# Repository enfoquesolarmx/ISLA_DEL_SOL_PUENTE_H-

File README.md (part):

# Isla del Sol — Puente H SPWM 48 V → 127 V / 60 Hz

Inversor / cargador de **puente H con modulación SPWM** para sistemas solares aislados: **48 V de batería → 127 V / 60 Hz, 1000 W**, con modo cargador de **1 kVA**.

El proyecto se publica como **referencia de estudio**: cada decisión de diseño está justificada y documentada (cálculos, hojas de datos, errores encontrados y cómo se corrigieron).

> ⚠️ **Advertencia de seguridad:** este equipo maneja corrientes altas en el lado de 48 V y **127 V AC en la salida, que pueden ser mortales**. Es un prototipo en desarrollo, no un producto certificado. Úsalo bajo tu propio riesgo y solo si tienes experiencia con electrónica de potencia.

---

*Tarjeta de potencia del puente H, prototipo de trinchera V0.1 (render 3D de KiCad). Detalles en [`hardware/puente_h/`](hardware/puente_h/README.md).*

*Tarjeta de transferencia de carga V0.1 (render 3D de KiCad): red / inversor / cargador con 5 relés y unión N–PE automática. Detalles en [`hardware/transferencia_reles/`](hardware/transferencia_reles/README.md).*

## Características principales

| Parámetro | Valor |
| --- | --- |
| Entrada | Batería de 48 V |
| Salida | 127 V / 60 Hz, 1000 W (transformador compatible 24–28 V / 120 V) |
| Modo inversor | Modulación híbrida: rama A a 24 kHz, rama B a 60 Hz |
| Modo cargador | Unipolar, ambas ramas a 24 kHz, 1 kVA |
| MOSFET | Infineon IRF100P219 (100 V), disipador Fischer SK 129 |
| Capacitores de bus | 4 × Rubycon 100ZLH820MEFC18X40 |
| Filtro de salida | ~2 mH (dispersión + inductor de ferrita E65 N87) + 4.7 µF MKP X2 |

---

## Gate drivers universales

Los módulos de gate driver son **intercambiables**: usan los mismos conectores (J1 hacia la tarjeta de control, J5 hacia el puente H) y **el mismo firmware**.

| Módulo | Tecnología | Tiempo muerto | Para qué | Estado |
| --- | --- | --- | --- | --- |
| IRS2186 | Driver de bootstrap | 500 ns | Producción, bajo costo | **Diseñado** (P9 en J1) |
| UCC21520DW | Driver aislado | 500 ns | Mejor desempeño | Diseñado |
| **TLP250 + tótem TIP41C/TIP42C** | Optoacoplador DIP + transistores TO-220 | **1 µs** | **Modo trinchera:** zonas sin acceso a componentes modernos; reparable con partes de tienda local | **V.0.1 diseñado** |
| **IR2110 + tótem TIP41C/TIP42C** | Driver de bootstrap legacy (DIP-14) + transistores TO-220 | **1 µs** | **Modo trinchera:** el driver de medio puente más fácil de conseguir o rescatar; reparable con partes de tienda local; de 1 a 5 MOSFET por posición | **V.0.1 diseñado** |

### Identificación automática del tiempo muerto (P9)

Cada módulo **declara** qué tiempo muerto necesita por la terminal **P9** de J1:

| P9 | Tiempo muerto |
| --- | --- |
| A GND | 500 ns (IRS2186, UCC21520) |
| Abierto o en falla | **1 µs** (TLP250, o cualquier duda) |

El modo seguro es el valor por defecto: un módulo legacy, un cable suelto o una soldadura fría nunca llevan a un tiempo muerto insuficiente.

### Diseño poka-yoke

El sistema está pensado para que **el error humano no pueda causar el daño**:

- Llave mecánica en la posición 8 de J5: el módulo solo entra en una posición.
- P9 abierto = 1 µs: falla segura.
- Serigrafía que dice qué hace cada módulo ("OPERACION DT TLP250=1US").
- Un solo firmware para los tres módulos: no hay versión equivocada que cargar.

---

## Contenido del repositorio

```
ISLA_DEL_SOL_PUENTE_H-/
├── README.md                                   ← este archivo
├── LICENSE.md                                  ← licencias (hardware, documentación, firmware)
├── CONTRIBUTING.md                             ← cómo se trabaja aquí: las reglas que ya costaron algo
├── .gitignore
├── docs/
│   ├── vision_isla_del_sol.md
│   ├── identificacion_dt_pin9.md
│   ├── modulacion_spwm.md
│   ├── decisiones_criticas.md                  ← bitácora de decisiones del arquitecto
│   ├── corte_por_hardware.md                   ← corte del PWM: SENSOR_OK, EN_HW, 74HC08
│   ├── referencia_outback_fx.md                ← estudio de referencia: OutBack FX (neutro común, unión N–PE)
│   ├── img/                                    ← diagramas (PNG, PDF y su script)
│   │   ├── README.md                           ← índice de diagramas
│   │   └── outback_fx/                         ← fotos de banco del OutBack FX
│   ├── compensacion_adaptativa_tiempo_muerto.md
│   └── sensado_corriente.md
└── hardware/
    ├── gate-drivers/
    │   ├── irs2186/
    │   │   ├── README.md
    │   │   └── GATE_DRIVER_IRS2186.kicad_pro / .kicad_sch / .kicad_pcb
    │   ├── ir2110-trinchera/
    │   │   ├── README.md
    │   │   └── GATE_DRIVER_IR2110_TOTEM.kicad_pro / .kicad_sch / .kicad_pcb
    │   ├── tlp250-trinchera/
    │   │   ├── README.md
    │   │   └── GATE_TLP_250_TOTEM_TIP.kicad_pro / .kicad_sch / .kicad_pcb
    │   └── ucc21520/
    │       ├── README.md                           ← borrador (faltan los archivos de KiCad)
    │       └── img/
    ├── puente_h/
    │   ├── README.md                               ← tarjeta de potencia
    │   ├── PUENTE_H_INV48V_REV_C_2026-10_GATE_CENTRO.kicad_pro / .kicad_sch / .kicad_pcb
    │   ├── CAPACITORES.kicad_sch                   ← hoja: banco de capacitores
    │   ├── DISIPADORES.kicad_sch                   ← hoja: disipadores
    │   ├── Heatsink_Fischer_SK129-STS_50.8mm.step  ← modelo 3D del disipador
    │   ├── Disipador_V8511Y_equiv.step             ← modelo 3D aproximado (versión anterior)
    │   ├── SSA2512_Littelfuse_Kelvin.kicad_mod     ← huella del shunt
    │   ├── SSA2512_Littelfuse.step                 ← modelo 3D del shunt
    │   ├── img/                                    ← vistas del PCB y 3D
    │   └── auditoria/
    │       ├── README.md                           ← auditoría de corriente y temperatura
    │       ├── auditoria_cobre.py · termica_componentes.py · sensibilidad.py
    │       └── resultados/                         ← figuras (.png) y resúmenes (.json)
    ├── control/
    │   ├── README.md                               ← tarjeta de control V0.1: glosario de módulos
    │   ├── ATMEGA328P_SPWM_TARJETA.kicad_pro / .kicad_sch / .kicad_pcb
    │   └── img/                                    ← esquemático, capas y vistas 3D
    ├── panel/
    │   ├── README.md                               ← panel frontal V0.2: LCD 16×2 / 20×4 I2C y 4 botones
    │   ├── PANEL_LCD_BOTONES.kicad_pro / .kicad_sch / .kicad_pcb
    │   ├── fp-lib-table + Isla_del_Sol.pretty/     ← huellas propias (ranuras M3 del LCD)
    │   └── img/                                    ← esquemático y vista del PCB
    ├── transferencia_reles/
    │   ├── README.md                               ← tarjeta de transferencia de carga V0.1
    │   ├── RELAY_TRANSFER_INV_RED.kicad_pro / .kicad_sch / .kicad_pcb
    │   ├── RELAY_TRANSFER_INV_RED.kicad_dru        ← reglas de separación (5 mm / 3 mm) para el DRC
    │   ├── 3d/                                     ← modelo 3D aproximado del relé (STEP) y su script
    │   ├── img/                                    ← esquemático, capas y vistas 3D
    │   └── auditoria/                              ← auditoría térmica a 10 A (script, mapas, informe)
    └── sensores/
        └── sensor-dc-ina-comparador/
            ├── README.md
            ├── SENSOR_DC_INA_COMPARADOR_V2.kicad_pro / .kicad_sch / .kicad_pcb   ← V0.2
            ├── SSA2512_Littelfuse_Kelvin.kicad_mod ← huella del shunt
            ├── SSA2512_Littelfuse.step             ← modelo 3D del shunt
            └── img/                                ← esquemático, PCB y evidencia del proceso
└── firmware/
    ├── auxiliar/                               ← AUX (A2): prueba del enlace I2C y panel (LCD, botonera, SETUP)
    └── critico/                                ← micro CRÍTICO (A1): SPWM, sensado, protecciones
        ├── README.md
        ├── ISLA_CRITICO/                       ← sketch de Arduino, un archivo por módulo
        │   ├── ISLA_CRITICO.ino
        │   ├── config_portadora.h / config_spwm.h
        │   ├── tabla_seno.h                    ← generado (cuarto de onda en flash)
        │   ├── spwm.h / spwm_328p.cpp          ← SPWM híbrida
        │   └── spwm_4809.cpp                   ← pendiente
        ├── herramientas/genera_tabla_seno.py
        └── pruebas/prueba_spwm.cpp             ← prueba en la PC del mismo spwm_328p.cpp
```

Próximamente: `hardware/sensores/` (sensor AC del primario).

### Documentos de sistema (`docs/`)

| Documento | Qué explica | Útil para |
| --- | --- | --- |
| [Visión: la Isla del Sol](docs/vision_isla_del_sol.md) | Por qué existe el proyecto: convertir la luz del sol en energía útil contra la cadena diaria del diésel (exploración, extracción, refinación, transporte); acceso a la electricidad como bien común; **la soberanía se construye en las trincheras** (soberanía energética: poder entender, reparar y sustituir cada pieza); hardware abierto y modo trinchera; lo que la solar también cuesta; ideas para trabajar más adelante (borrador) | Entender el propósito antes que los circuitos |
| [Identificación del tiempo muerto por P9](docs/identificacion_dt_pin9.md) | Cómo cada módulo declara su tiempo muerto (P9 a GND = 500 ns, abierto = 1 µs); soporte legacy para trincheras; costo contra beneficio; filosofía poka-yoke; llave mecánica en la posición 8; análisis de fallas; código de referencia para ATmega328 y ESP32; validación en banco | Entender la interfaz universal y escribir el firmware |
| [Modulación SPWM: bipolar, unipolar e híbrida](docs/modulacion_spwm.md) | Por qué el inversor usa modulación **híbrida** (pierna A a 24 kHz, pierna B a 60 Hz) y el cargador **unipolar**; comparación de rizo (4 : 2 : 1), consumo en vacío, pérdidas de conmutación, distorsión por tiempo muerto con módulos de 500 ns y 1 µs, modo común; ciclos de trabajo para el firmware; validación | Entender la estrategia de modulación y escribir el firmware |
| [La base de tiempo del SPWM, línea por línea](docs/base_de_tiempo_spwm.md) | **La receta para repartir cada tick del reloj:** explica y justifica cada constante de `config_portadora.h` y `config_spwm.h` (TOP, muestras, cuarto de onda, tiempo muerto, pulso mínimo, techo del 95 % y amplitud máxima) con sus fórmulas paso a paso, los candados del compilador y lo medido en banco. La misma metodología aplicada a otros micros (Nano Every, Bluepill, ESP32) |
| [Decisiones críticas de diseño](docs/decisiones_criticas.md) | Bitácora de decisiones del arquitecto (ADR): **por qué** se eligió cada solución, qué alternativas se descartaron y qué críticas se esperan. Entradas **DC-001 a DC-019**: cascada de alimentación 48 → 15 → 8 → 5 V ("pagamos complejidad para comprar pureza en el ADC"), XL7015 en socket mixto, protección de la entrada de 48 V, MP1584, 7805, sensado AC y de la batería, tablero de diagnóstico, holgura para capacidad médica (DC-009), reparto de tareas entre los dos ATmega con I2C y CAN (DC-010), lectura de P9 (DC-011), alimentación de los Arduino Nano (DC-012), pinza SCT-013 (DC-013), **corte del PWM por hardware** (DC-014), corriente de fuga para la V2 (DC-015), **corto circuito en AC, arranque de motores y arco** (DC-016), presupuesto de CPU/memoria y Nano Every (DC-017), **cargador híbrido y socket 328P/4809** (DC-018) y **transferencia red / inversor / cargador con 5 relés, modos INVERSOR CASA (con unión N–PE) e INVERSOR CARGA (UPS, sin unión)** (DC-019) | Entender lo que no se ve en el cobre antes de "mejorar" algo |
| [Corte del PWM por hardware](docs/corte_por_hardware.md) | Cómo el inversor se apaga en ~2–4 µs sin pedir permiso al firmware: barrera **74HC08 (AND, nunca 74HC00)**, EN_HW (D12 + switch ON/OFF + pull-down), lógica fail-safe **SENSOR_OK** (sensor ausente o cable roto = corte), jumper **J_RIESGO**, doble candado AUX/CRÍTICO; cada componente con su porqué, cálculos, firmware mínimo, serigrafía, prueba en banco y diagnóstico | Antes de soldar, probar o "mejorar" la protección del puente H |
| [Referencia industrial: OutBack FX](docs/referencia_outback_fx.md) | Estudio en banco de la etapa AC de un OutBack FX 120 V: **neutro común**, tierra de chasis pasante, **sin unión N–PE interna** (la decide el instalador, NOM 250-24 / 250-30); filtro C1 5 µF + toroide en el neutro; relé Deltrol 3PDT con clasificación HP; guía de los 4 casos de instalación; comparación con la V1 de 5 relés y sus modos **INVERSOR CASA / INVERSOR CARGA** configurados por menú y selector SW_TN | Entender la unión N–PE de la V1 y preparar la versión de bajo costo |
| [Compensación adaptativa de tiempo muerto](docs/compensacion_adaptativa_tiempo_muerto.md) | Por qué el tiempo muerto genera armónicos impares; compensación con el signo de la corriente; medición del 3er armónico con Goertzel; ajuste automático; hoja de ruta en 5 etapas | Etapa posterior: mejorar la calidad de la onda |
| [Sensado de corriente DC y AC](docs/sensado_corriente.md) | Por qué hacen falta dos sensores (bus DC y primario AC); protección por hardware; INA240 en el primario; protección del transformador contra saturación; muestreo sincronizado; calibración | Etapa posterior: base para el control avanzado |

### Módulos gate driver (`hardware/gate-drivers/`)

Todos son **gate drivers de medio puente H** (una rama: MOSFET alto + MOSFET bajo). El puente completo usa dos módulos iguales, uno por rama.

| Módulo | Documento | Archivos KiCad | Qué incluye |
| --- | --- | --- | --- |
| **IRS2186** | [README](hardware/gate-drivers/irs2186/README.md) | ✓ Esquemático (por bloques A–F con notas), PCB y proyecto | Interfaz con P9 a GND; tierras compartidas (lógica = potencia), unión única GND_K–GND con *net tie* y cómo controlar el lazo de tierra; bootstrap ES1D → R 2.2 Ω → VB con referencias; cálculo de los 500 ns; **alcance por cantidad de MOSFET** (1 IRF100P219 o hasta 2 IRF540N); opciones con tótem; lista de materiales; validación |
| **TLP250 + tótem TIP41C/TIP42C** (trinchera) | [README](hardware/gate-drivers/tlp250-trinchera/README.md) | ✓ Esquemático (por bloques A–I con **guía rápida de trinchera**: TLP250 contra TLP250H, ensamble y prueba sin MOSFET), PCB y proyecto | Propósito educativo y de supervivencia; entrada aislada; por qué 1 µs; tótem y regla de 250 nC; **evaluación de 9 transistores** (por qué TIP41/42 y no BD, Darlington, IRF540 o BC); layout; BOM; ensamble con RTV neutro; validación en 10 pasos; **registro de errores corregidos durante el diseño** |
| **UCC21520DW** | [README](hardware/gate-drivers/ucc21520/README.md) | ✓ Esquemático (por bloques), PCB y proyecto | Driver aislado de dos canales (4 A / 6 A), protección contra entradas encimadas, bootstrap; P9 a GND (500 ns). **R3 = 49.9 kΩ**: 500 ns de respaldo por hardware (el driver aplica el mayor entre firmware y R3, no la suma). **UCC21520DW** (UVLO 8 V), no la versión A (5 V) |
| **IR2110 + tótem TIP41C/TIP42C** (trinchera) | [README](hardware/gate-drivers/ir2110-trinchera/README.md) | ✓ Esquemático (por bloques A–I con **guía rápida de trinchera**: ensamble y prueba sin MOSFET), PCB y proyecto | VSS y COM separados con J5-6 a GND lógico; VDD de 5 V con 78L05; SD a VSS; tótem por canal con su desacoplo; zener en VB–VS1 y en VCC; P9 abierto (1 µs); **alcance de 1 a 5 MOSFET** y refuerzo del bootstrap; **registro de 8 errores corregidos**; BOM; validación |

### Tarjeta de potencia (`hardware/puente_h/`)

| Tarjeta | Documento | Archivos KiCad | Qué incluye |
| --- | --- | --- | --- |
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
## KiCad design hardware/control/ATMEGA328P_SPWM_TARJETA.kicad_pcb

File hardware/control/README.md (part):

# Tarjeta de control V0.1: el cerebro de la Isla del Sol

La tarjeta de control lleva **dos microcontroladores** (módulos Arduino Nano con ATmega328P) y todo lo que necesitan alrededor:
- la alimentación de 48 V a 15, 8 y 5 V;
- los sensores de voltaje, corriente y temperatura;
- el corte del PWM por hardware;
- las órdenes a la tarjeta de transferencia;
- el CAN con el BMS, la pantalla, el ventilador y el buzzer.

> **Para quien arma y repara en la trinchera:** este documento es un **glosario de módulos**. Cada bloque de la tarjeta dice **qué hace**, **por qué existe**, **por qué cada pieza tiene ese valor** y **qué pasa si esa pieza falla**. Cuando algo no funcione, busca el bloque, mide en su test point y compara con la tabla.

*Vista superior en 3D (KiCad 9), serigrafía "TARJETA DE CONTROL SPWM · ISLA DEL SOL · VER 0.1.J.G NOV 2026". Los dos microcontroladores van en zócalo (aquí se ven los zócalos vacíos), igual que el 74HC08. La serigrafía indica el uso de cada conector, los valores de referencia y los sustitutos de trinchera.*

*Esquemático por bloques (KiCad 9, hoja A2). Cada marco azul es uno de los módulos de este glosario.*

---

## 0. Mapa de la tarjeta

| # | Módulo | Microcontrolador | Decisión | En una frase |
| --- | --- | --- | --- | --- |
| 1 | [Microcontroladores CRÍTICO y AUX](#1-microcontroladores-crítico-y-aux) · [**Mapa de pines**](#11-mapa-de-pines) | — | DC-010, DC-012, DC-017 | El CRÍTICO genera la onda y protege; el AUX informa y conversa |
| 2 | [Entrada de 48 V y su protección](#2-entrada-de-48-v-y-su-protección) | — | DC-003 | Que un pico de la batería no queme el buck |
| 3 | [Buck 48 → 15 V (XL7015)](#3-buck-48--15-v-xl7015) | — | DC-002 | El riel de drivers, relés y ventilador |
| 4 | [Buck 15 → 8 V (MP1584)](#4-buck-15--8-v-mp1584) | — | DC-004 | Baja el voltaje para que el 7805 vaya frío |
| 5 | [Regulador 5 V (7805)](#5-regulador-5-v-7805) | — | DC-005 | 5 V limpio: es la referencia del ADC |
| 6 | [Tablero de LEDs y test points](#6-tablero-de-leds-y-test-points) | — | DC-008 | Dónde está la falla y qué tan mal está |
| 7 | [Monitor del riel de 15 V](#7-monitor-del-riel-de-15-v) | AUX (A1) | DC-008 | Ve envejecer la fuente antes de que falle |
| 8 | [Sensado AC del inversor](#8-sensado-ac-del-inversor-y-de-la-red) | CRÍTICO (A0) | DC-006 | Lazo de amplitud de la salida |
| 9 | [Sensado AC de la red](#8-sensado-ac-del-inversor-y-de-la-red) | CRÍTICO (A6) | DC-006 | Sincronía antes de transferir |
| 10 | [Corriente AC con pinza SCT-013](#9-corriente-ac-con-pinza-sct-013-015) | CRÍTICO (A2) | DC-013 | Watts, sobrecarga y tiempo muerto |
| 11 | [Voltaje de batería](#10-voltaje-de-batería) | CRÍTICO (A3) | DC-007 | Bajo voltaje y estado de carga |
| 12 | [Temperatura (NTC)](#11-temperatura-ntc-10-k) | CRÍTICO (A1) | — | Derrateo y paro por calor |
| 13 | [Corte del PWM por hardware](#12-corte-del-pwm-por-hardware) | CRÍTICO / AUX | DC-014 | Apaga los MOSFET sin esperar al firmware |
| 14 | [Lectura de P9](#13-lectura-de-p9-tiempo-muerto) | CRÍTICO (A7) | DC-011 | Qué gate driver hay y qué tiempo muerto pide |
| 15 | [Límite de corriente I_LIM](#14-límite-de-corriente-i_lim) | CRÍTICO (D2) | DC-016 | Deja arrancar motores sin disparar el corte |
| 16 | [Órdenes a la tarjeta de transferencia (J15)](#15-órdenes-a-la-tarjeta-de-transferencia-j15) | CRÍTICO (D4–D6) | DC-019 | Red, inversor, cargador y unión N–PE |
| 17 | [Caída automática a la red](#16-caída-automática-a-la-red) | — | DC-019 | Si el inversor se corta, la casa vuelve a la red sola |
| 18 | [CAN con el BMS](#17-can-con-el-bms) | AUX (SPI) | DC-010 | Lo que la batería permite cargar y descargar |
| 19 | [Pantalla LCD y botonera](#18-pantalla-lcd-162-y-botonera) | AUX (D4, D5, A7) | — | Menú del SETUP y estado |
| 20 | [Ventilador](#19-ventilador) | AUX (D6) | — | Enfría el puente H |
| 21 | [Buzzer y LED de alarma](#20-buzzer-y-led-de-alarma) | AUX (D8) | — | Avisa sin que nadie mire la pantalla |
| 22 | [Salidas de 15 V y 5 V](#21-salidas-de-15-v-y-5-v) | — | — | Alimentan los gate drivers y módulos externos |

**Regla general de las resistencias de 1 kΩ en serie:** casi todas las señales que salen de la tarjeta por un cable pasan por **1 kΩ antes del pin del microcontrolador** (R3, R15, R19, R22, R25, R38, R39, R41). Si el cable se pela contra 15 V o recibe un pico, esa resistencia limita la corriente que entra a los diodos internos del ATmega a unos pocos mA, y el pin sobrevive. **No se quitan "porque sobran".**

**Regla general de las resistencias de 10 kΩ a GND (pull-down) o a 5 V (pull-up):** fijan el estado de una línea cuando nadie la maneja: microcontrolador en reset, cable suelto, módulo ausente. **El estado que fijan es siempre el seguro:** apagado, sin orden o casa en la red.

---

## 1. Microcontroladores CRÍTICO y AUX

> **Lo que decide la onda y la protege vive en un solo microcontrolador. Lo que informa y conversa vive en el otro.** (DC-010)

| Ref. | Valor | Qué hace | Por qué |
| --- | --- | --- | --- |
| **A1** | Arduino Nano (ATmega328P), **CRÍTICO** | SPWM (D9, D10, D11, D3), sensado AC y DC, relés, corte, P9, I_LIM | Todo lo que tiene que ocurrir **dentro del periodo de la portadora** de 24 kHz. No puede depender de un enlace |
| **A2** | Arduino Nano (ATmega328P), **AUX** | CAN/BMS, LCD, botonera, ventilador, buzzer, SENSOR_OK, AUX_KILL, monitor de 15 V | Lo que no es tiempo real. Si se cuelga, la onda sigue y el CRÍTICO protege solo |
| **R10, R11** | 4.7 kΩ a 5 V | Pull-ups del enlace I2C entre los dos (A4/A5) | El I2C es de drenaje abierto: sin pull-up nunca sube. 4.7 kΩ da un flanco de ~0.4 µs (máximo permitido 1 µs a 100 kHz). **Un solo par para todo el bus** |
| **C15, C19** | 1 µF | Desacople junto al pin +5V de cada Nano | Los Nano se alimentan por **+5V (pin 27), nunca por VIN** (DC-012): VIN pasa por otro regulador que necesita ≥7 V. El 1 µF da la corriente de los picos de conmutación del chip |

- **Los dos van en zócalo:** se cambian sin soldar, y el mismo zócalo acepta un **Nano Every (ATmega4809)** con otro firmware (DC-017, DC-018).
- **Si el enlace I2C se cae:** el AUX manda un latido cada ~100 ms. Si el CRÍTICO no lo recibe en ~500 ms, **deja de cargar** y sigue protegiendo la batería con su propia lectura.

### 1.1 Mapa de pines

> **Fuente de verdad para el firmware.** Verificado pin por pin contra el esquemático (`ATMEGA328P_SPWM_TARJETA.kicad_sch`, 2026-11-13): cada red de esta tabla es la que tiene el pin en KiCad. Si cambia el esquemático, **se actualiza esta tabla en el mismo cambio**.

**Columnas:**
- **Al encender:** cómo debe quedar el pin desde la primera línea de `setup()`, antes que cualquier otra cosa.
- **Dueño:** el timer o periférico que lo controla; ningún otro módulo del firmware debe tocarlo.

#### CRÍTICO (A1): tiempo real, SPWM y protección

| Pin | Red (KiCad) | Función | E/S | Al encender | Dueño | Sección |
| --- | --- | --- | --- | --- | --- | --- |
| D0 / D1 | — | Puerto serie (USB, carga del firmware, reporte) | — | Libre para `Serial` | USART | — |
| **D2** | `CRIT_D2_ILIM` | **I_LIM:** 0 V = en el límite de corriente → bajar la modulación | Entrada (INT0) | Entrada, **sin** pull-up interno (R40 externo) | INT0 | [14](#14-límite-de-corriente-i_lim) |
| **D3** | `LB_IN` | **LB:** pierna B, lado bajo (60/50 Hz) → 74HC08 | Salida | **BAJO** | ISR del Timer1 | [12](#12-corte-del-pwm-por-hardware) |
| **D4** | `INV_D4` | **INV_CMD:** la casa pasa al inversor (K4 + K2), vía R39 | Salida | **BAJO** (casa en la red) | Lógica de transferencia | [15](#15-órdenes-a-la-tarjeta-de-transferencia-j15), [16](#16-caída-automática-a-la-red) |
| **D5** | `CARG_CMD` | **CARG_CMD:** el transformador se conecta a la red para cargar (K1 + K3) | Salida | **BAJO** | Lógica de transferencia | [15](#15-órdenes-a-la-tarjeta-de-transferencia-j15) |
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
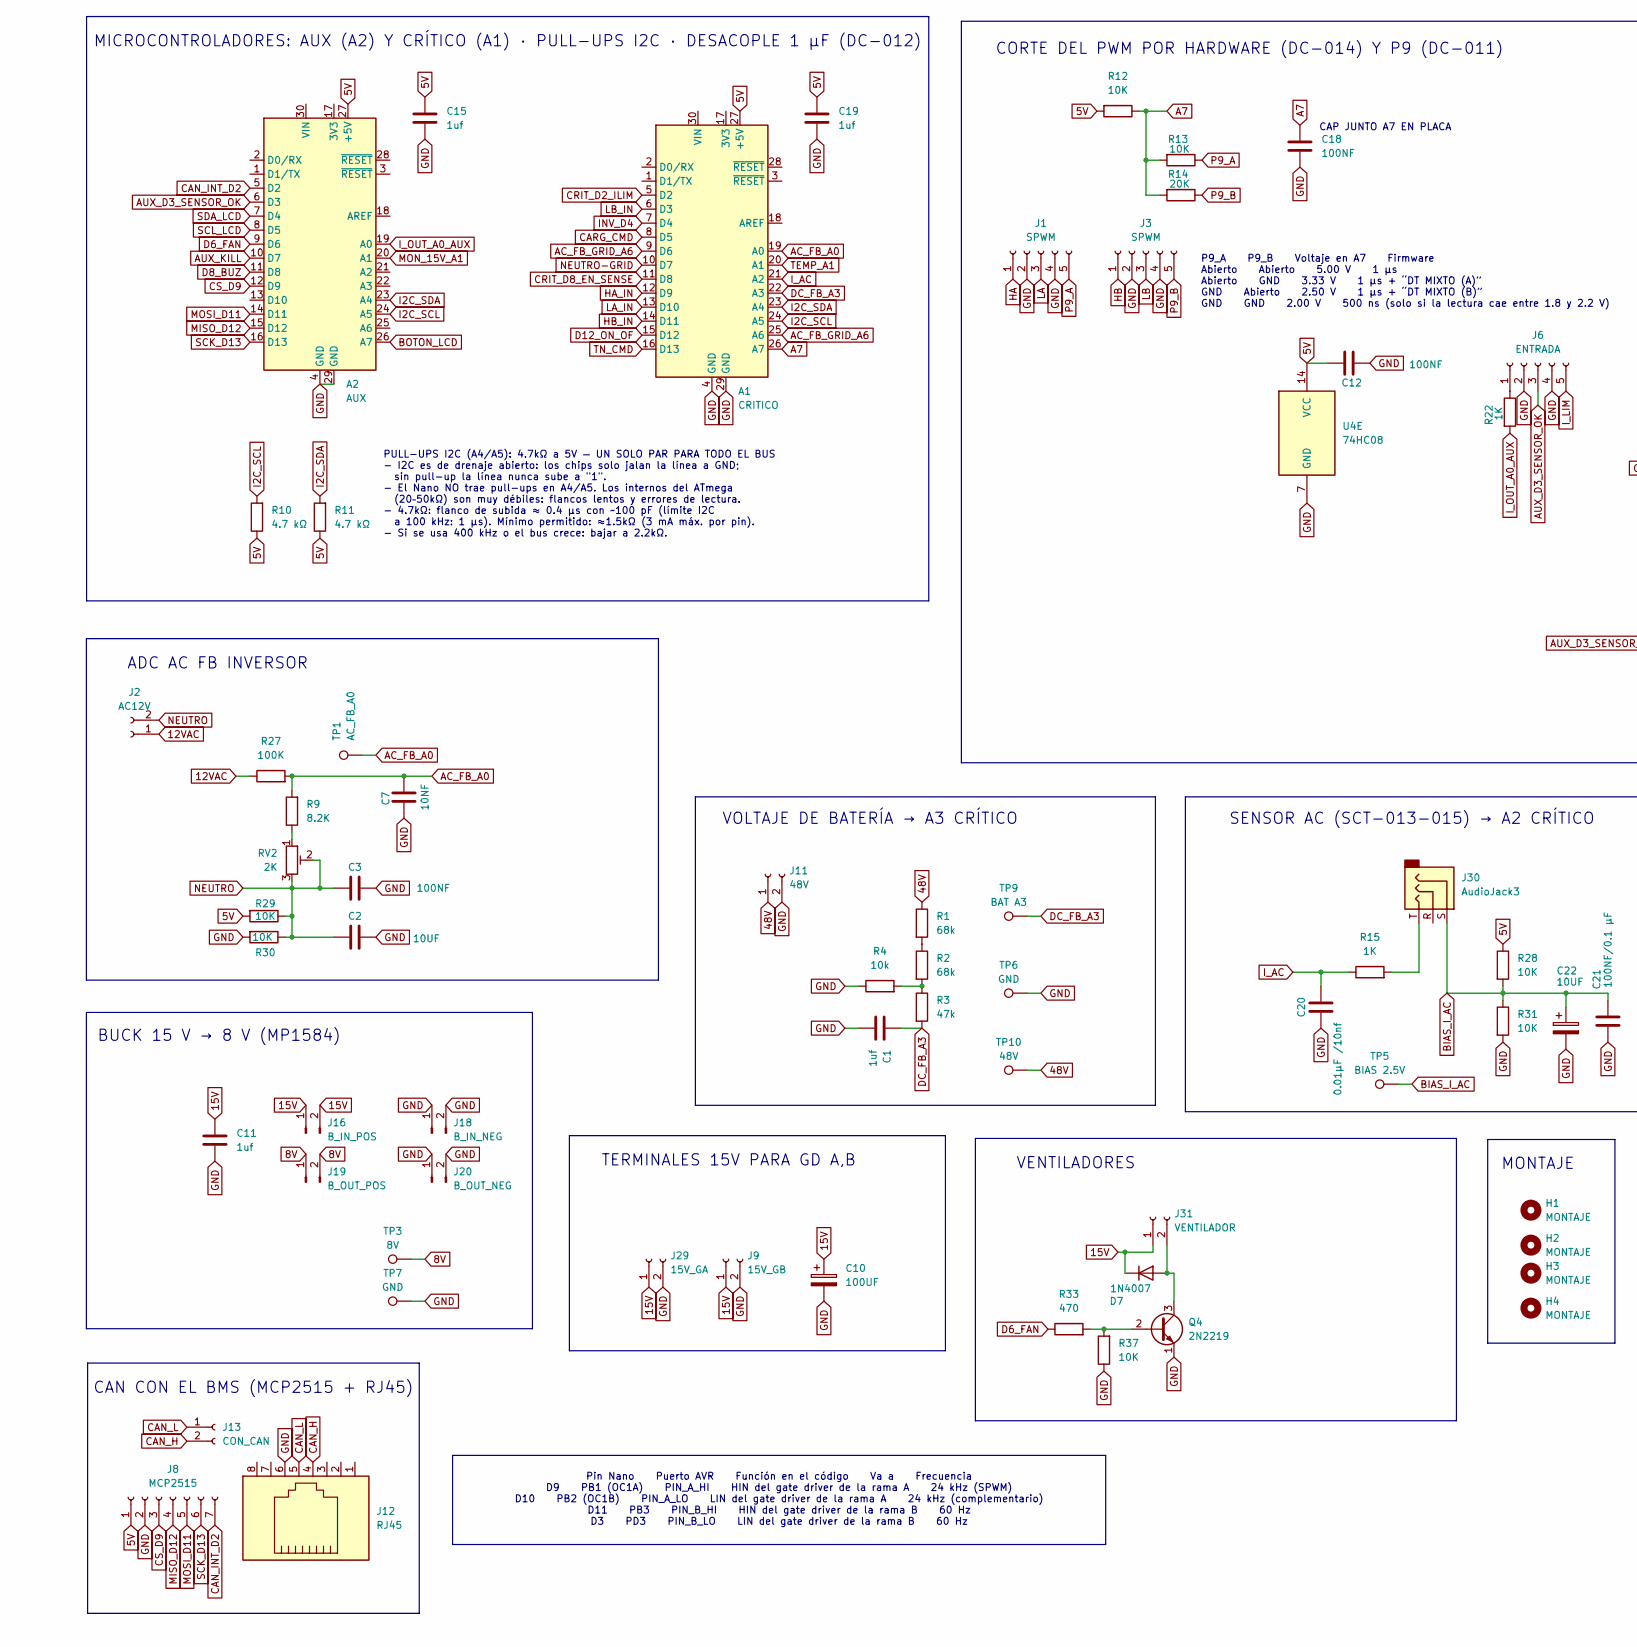
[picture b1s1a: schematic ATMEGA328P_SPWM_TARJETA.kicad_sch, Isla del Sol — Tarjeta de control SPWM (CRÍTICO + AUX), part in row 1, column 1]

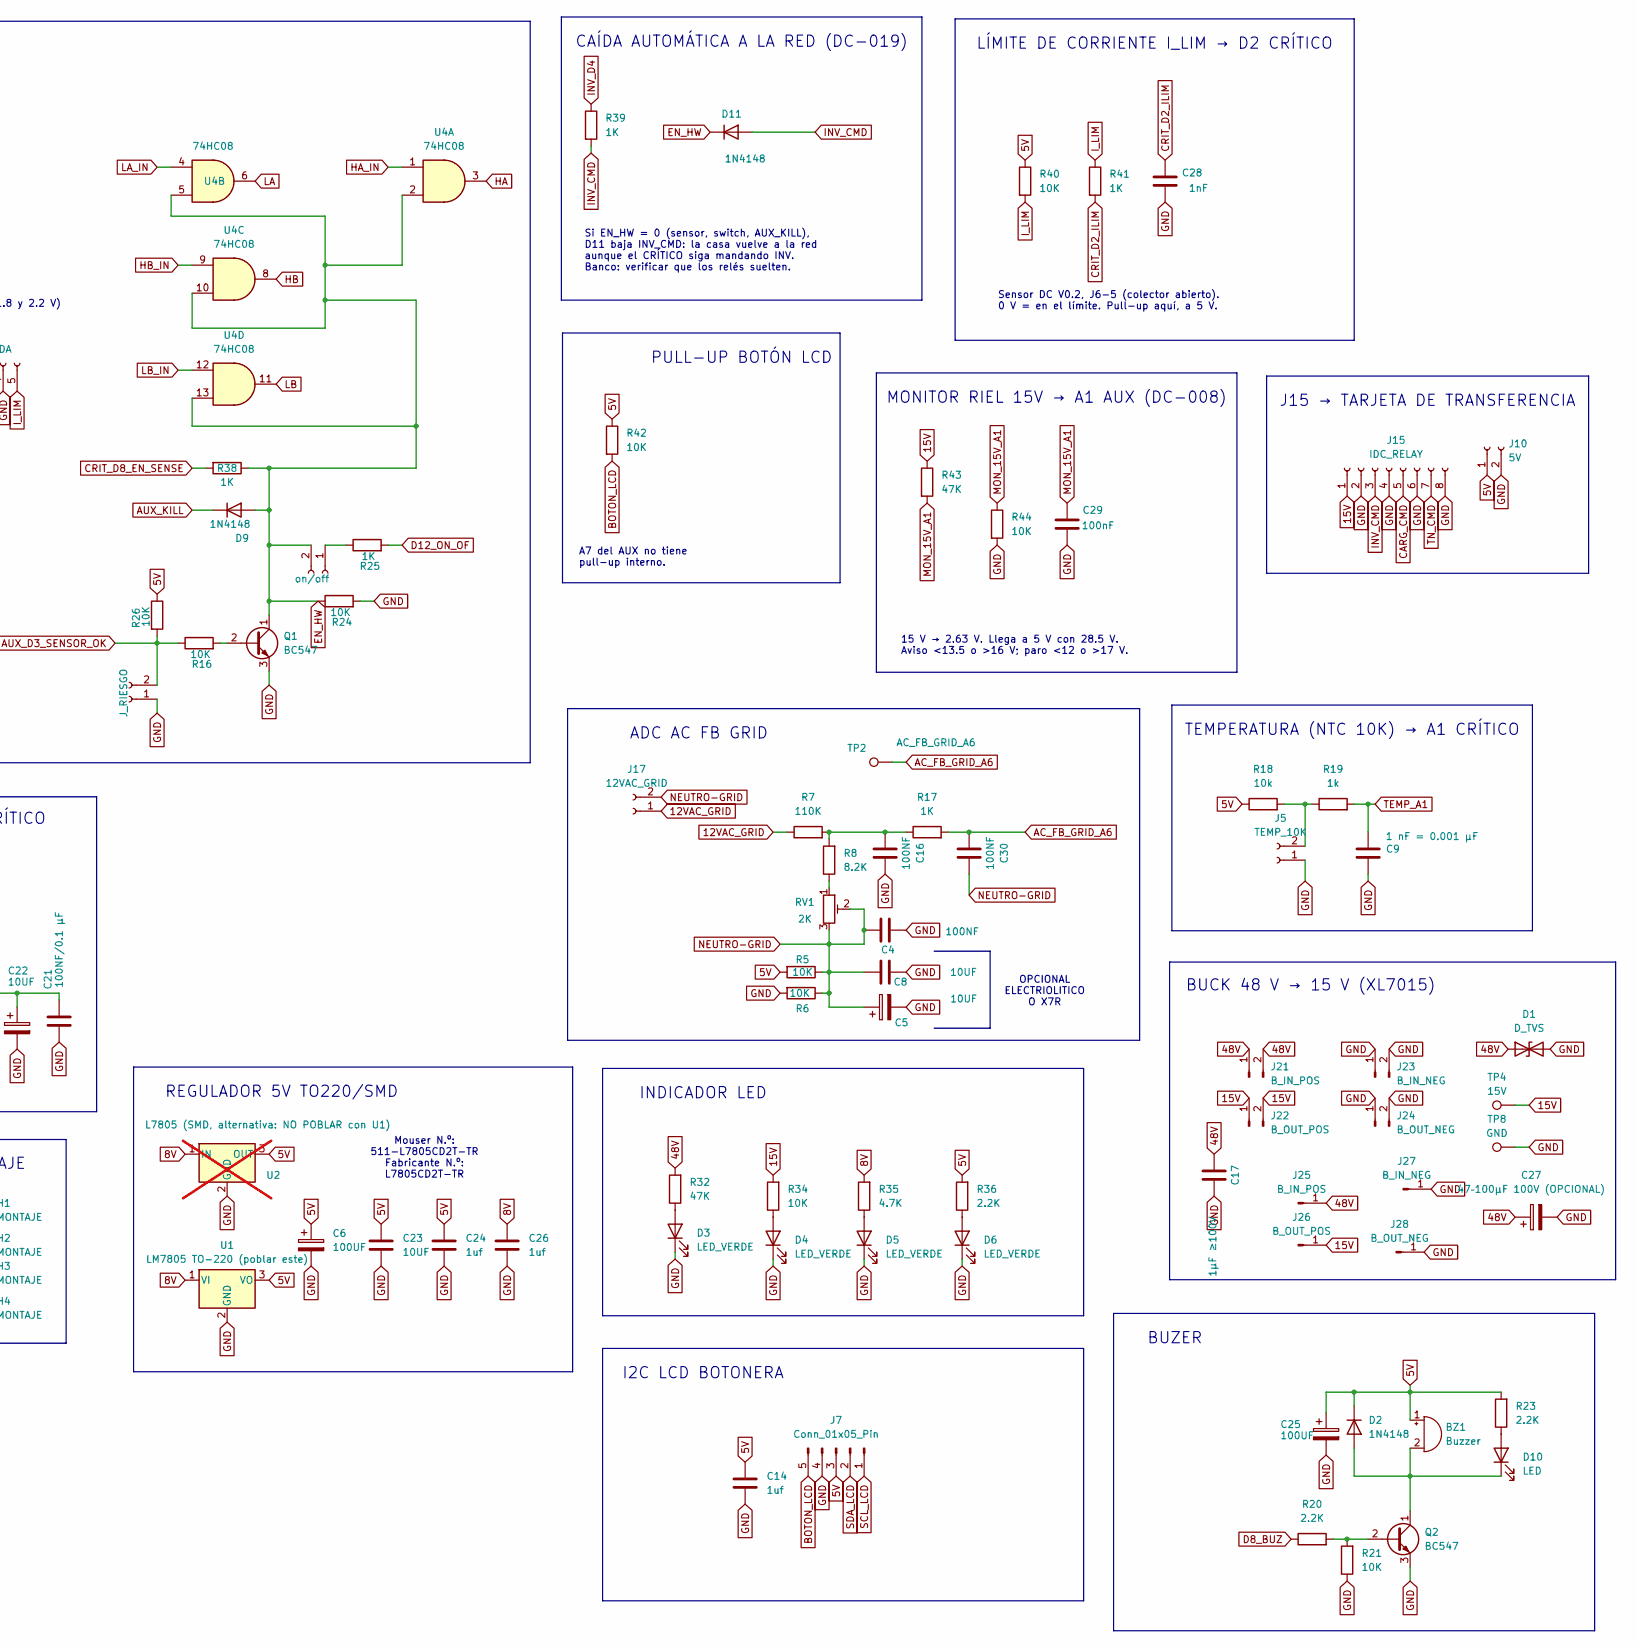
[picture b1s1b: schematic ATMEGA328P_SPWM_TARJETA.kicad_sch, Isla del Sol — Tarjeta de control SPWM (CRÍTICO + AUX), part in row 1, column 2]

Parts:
A1: CRITICO; Arduino_Nano
A2: AUX; Arduino_Nano
BZ1: Buzzer; Buzzer_12x9.5RM7.6
C1, C11, C14, C15, C19, C24, C26: 1uf; C_1206_3216Metric
C2, C8, C23: 10UF; C_1206_3216Metric
C3, C4, C16, C18, C30: 100NF; C_1206_3216Metric
C5: 10UF; CP_Radial_D5.0mm_P2.50mm
C6, C10: 100UF; CP_Radial_D10.0mm_P5.00mm
C7: 10NF; C_1206_3216Metric
C9: 1 nF = 0.001 µF; C_Disc_D3.0mm_W2.0mm_P2.50mm
C12: 100NF; C_Disc_D3.0mm_W2.0mm_P2.50mm
C17: 1µF ≥100V; C_1210_3225Metric_Pad1.33x2.70mm_HandSolder
C20: 0.01µF /10nf; C_Disc_D3.0mm_W1.6mm_P2.50mm
C21: 100NF/0.1 µF; C_Disc_D3.0mm_W1.6mm_P2.50mm
C22: 10UF; CP_Radial_D8.0mm_P3.50mm
C25: 100UF; CP_Radial_D8.0mm_P3.50mm
C27: 47–100µF 100V (OPCIONAL); CP_Elec_10x10
C28: 1nF; C_Disc_D3.0mm_W2.0mm_P2.50mm
C29: 100nF; C_Disc_D3.0mm_W2.0mm_P2.50mm
D1: D_TVS; D_SMB
D2, D9, D11: 1N4148; D_DO-35_SOD27_P7.62mm_Horizontal
D3, D4, D5, D6: LED_VERDE; LED_1206_3216Metric
D7: 1N4007; D_DO-41_SOD81_P10.16mm_Horizontal
D10: LED; LED_D3.0mm_Clear
H1, H2, H3, H4: MONTAJE; MountingHole_2.7mm_M2.5
J1, J3: SPWM; PhoenixContact_SPT_1.5_5-H-3.5_1x05_P3.5mm_Horizontal
J2: AC12V; TerminalBlock_MaiXu_MX126-5.0-02P_1x02_P5.00mm
J4: on/off; PinHeader_1x02_P2.54mm_Vertical
J5: TEMP_10K; PinHeader_1x02_P2.54mm_Vertical
J6: ENTRADA; PhoenixContact_SPT_1.5_5-H-3.5_1x05_P3.5mm_Horizontal
J7: Conn_01x05_Pin; PinHeader_1x05_P2.54mm_Vertical
J8: MCP2515; PinHeader_1x07_P2.54mm_Vertical
J9: 15V_GB; JST_EH_B2B-EH-A_1x02_P2.50mm_Vertical
J10: 5V; JST_EH_B2B-EH-A_1x02_P2.50mm_Vertical
J11: 48V; TerminalBlock_MaiXu_MX126-5.0-02P_1x02_P5.00mm
J12: RJ45; RJ45_OST_PJ012-8P8CX_Vertical
J13: CON_CAN; PinHeader_1x02_P2.54mm_Vertical
J14: J_RIESGO; PinHeader_1x02_P2.54mm_Vertical
J15: IDC_RELAY; IDC-Header_2x04_P2.54mm_Vertical
J16, J21: B_IN_POS; PinHeader_1x02_P2.54mm_Vertical
J17: 12VAC_GRID; TerminalBlock_MaiXu_MX126-5.0-02P_1x02_P5.00mm
J18, J23: B_IN_NEG; PinHeader_1x02_P2.54mm_Vertical
J19, J22: B_OUT_POS; PinHeader_1x02_P2.54mm_Vertical
J20, J24: B_OUT_NEG; PinHeader_1x02_P2.54mm_Vertical
J25: B_IN_POS; PinHeader_1x01_P2.54mm_Vertical
J26: B_OUT_POS; PinHeader_1x01_P2.54mm_Vertical
J27: B_IN_NEG; PinHeader_1x01_P2.54mm_Vertical
J28: B_OUT_NEG; PinHeader_1x01_P2.54mm_Vertical
J29: 15V_GA; JST_EH_B2B-EH-A_1x02_P2.50mm_Vertical
J30: AudioJack3; Jack_3.5mm_CUI_SJ1-3533NG_Horizontal_CircularHoles
J31: VENTILADOR; JST_EH_B2B-EH-A_1x02_P2.50mm_Vertical
Q1: BC547; TO-92_Inline
Q2: BC547; TO-92_Inline_Wide
Q4: 2N2219; TO-39-3
R1, R2: 68k; R_Axial_DIN0204_L3.6mm_D1.6mm_P5.08mm_Horizontal
R3: 47k; R_Axial_DIN0204_L3.6mm_D1.6mm_P5.08mm_Horizontal
R4, R18: 10k; R_Axial_DIN0204_L3.6mm_D1.6mm_P5.08mm_Horizontal
R5, R6, R12, R13, R16, R21, R24, R26, R28, R29, R30, R31, R34, R37, R40, R42, R44: 10K; R_Axial_DIN0204_L3.6mm_D1.6mm_P5.08mm_Horizontal
R7: 110K; R_Axial_DIN0204_L3.6mm_D1.6mm_P5.08mm_Horizontal
R8, R9: 8.2K; R_Axial_DIN0204_L3.6mm_D1.6mm_P5.08mm_Horizontal
R10, R11: 4.7 kΩ; R_Axial_DIN0204_L3.6mm_D1.6mm_P5.08mm_Horizontal
R14: 20K; R_Axial_DIN0204_L3.6mm_D1.6mm_P5.08mm_Horizontal
R15, R17, R22, R25, R38, R39, R41: 1K; R_Axial_DIN0204_L3.6mm_D1.6mm_P5.08mm_Horizontal
R19: 1k; R_Axial_DIN0204_L3.6mm_D1.6mm_P5.08mm_Horizontal
R20, R23, R36: 2.2K; R_Axial_DIN0204_L3.6mm_D1.6mm_P5.08mm_Horizontal
R27: 100K; R_Axial_DIN0204_L3.6mm_D1.6mm_P5.08mm_Horizontal
R32, R43: 47K; R_Axial_DIN0204_L3.6mm_D1.6mm_P5.08mm_Horizontal
R33: 470; R_Axial_DIN0204_L3.6mm_D1.6mm_P5.08mm_Horizontal
R35: 4.7K; R_Axial_DIN0204_L3.6mm_D1.6mm_P5.08mm_Horizontal
RV1, RV2: 2K; Potentiometer_Bourns_3296W_Vertical
TP1: AC_FB_A0; TestPoint_Loop_D2.50mm_Drill1.0mm_LowProfile
TP2: AC_FB_GRID_A6; TestPoint_Loop_D2.50mm_Drill1.0mm_LowProfile
TP3: 8V; TestPoint_Loop_D2.50mm_Drill1.0mm_LowProfile
TP4: 15V; TestPoint_Loop_D2.50mm_Drill1.0mm_LowProfile
TP5: BIAS 2.5V; TestPoint_Loop_D2.50mm_Drill1.0mm_LowProfile
TP6, TP7, TP8: GND; TestPoint_Loop_D2.50mm_Drill1.0mm_LowProfile
TP9: BAT A3; TestPoint_Loop_D2.50mm_Drill1.0mm_LowProfile
TP10: 48V; TestPoint_Loop_D2.50mm_Drill1.0mm_LowProfile
U1: LM7805 TO-220 (poblar este); TO-220-3_Horizontal_TabDown
U2: L7805 (SMD, alternativa: NO POBLAR con U1); TO-252-2; not fitted
U4: 74HC08; DIP-14_W7.62mm_Socket

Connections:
5V: A1.27 (+5V), A2.27 (+5V), BZ1.1 (+), C6.1, C12.1, C14.1, C15.1, C19.1, C23.1, C24.1, C25.1, D2.1 (K), J7.3, J8.1, J10.1, R5.2, R10.1, R11.1, R12.2, R18.1, R23.2, R26.1, R28.1, R29.2, R36.2, R40.1, R42.1, U1.3 (VO), U2.3 (OUT), U4.14 (VCC)
8V: C26.1, J19.1, J19.2, R35.2, TP3.1 (1_1), U1.1 (VI), U2.1 (IN)
12VAC: J2.1, R27.1
12VAC_GRID: J17.1, R7.1
15V: C10.1, C11.1, D7.1 (K), J9.1, J15.1, J16.1, J16.2, J22.1, J22.2, J26.1 (Pin_1_1), J29.1, J31.1, R34.2, R43.1, TP4.1 (1_1)
48V: C17.1, C27.1, D1.1 (A1), J11.1, J21.1, J21.2, J25.1 (Pin_1_1), R1.1, R32.2, TP10.1 (1_1)
A7: A1.26 (A7), C18.1, R12.1, R13.2, R14.2
AC_FB_A0: A1.19 (A0), C7.1, R9.2, R27.2, TP1.1 (1_1)
AC_FB_GRID_A6: A1.9 (D6), A1.25 (A6), C30.1, R17.2, TP2.1 (1_1)
AUX_D3_SENSOR_OK: A2.6 (D3), J6.3, J14.2, R16.1, R26.2
AUX_KILL: A2.10 (D7), D9.1 (K)
BIAS_I_AC: C21.1, C22.1, J30.S, R28.2, R31.1, TP5.1 (1_1)
BOTON_LCD: A2.26 (A7), J7.5, R42.2
CAN_H: J12.4, J13.2
CAN_INT_D2: A2.5 (D2), J8.7
CAN_L: J12.5, J13.1
CARG_CMD: A1.8 (D5), J15.5
CRIT_D2_ILIM: A1.5 (D2), C28.1, R41.2
CRIT_D8_EN_SENSE: A1.11 (D8), R38.2
CS_D9: A2.12 (D9), J8.3
D6_FAN: A2.9 (D6), R33.1
D8_BUZ: A2.11 (D8), R20.1
D12_ON_OF: A1.15 (D12), R25.2
DC_FB_A3: A1.22 (A3), C1.1, R3.2, TP9.1 (1_1)
EN_HW: D9.2 (A), D11.1 (K), J4.2, Q1.1 (C), R24.1, R38.1, U4.2, U4.5, U4.10, U4.13
GND: A1.4 (GND), A1.29 (GND), A2.4 (GND), A2.29 (GND), C1.2, C2.2, C3.2, C4.2, C5.2, C6.2, C7.2, C8.2, C9.2, C10.2, C11.2, C12.2, C14.2, C15.2, C16.2, C17.2, C18.2, C19.2, C20.2, C21.2, C22.2, C23.2, C24.2, C25.2, C26.2, C27.2, C28.2, C29.2, D1.2 (A2), D3.1 (K), D4.1 (K), D5.1 (K), D6.1 (K), J1.2, J1.4, J3.2, J3.4, J5.1, J6.2, J6.4, J7.4, J8.2, J9.2, J10.2, J11.2, J12.6, J14.1, J15.2, J15.4, J15.6, J15.8, J18.1, J18.2, J20.1, J20.2, J23.1, J23.2, J24.1, J24.2, J27.1 (Pin_1_1), J28.1 (Pin_1_1), J29.2, Q1.3 (E), Q2.3 (E), Q4.1 (E), R4.1, R6.2, R21.1, R24.2, R30.2, R31.2, R37.1, R44.2, TP6.1 (1_1), TP7.1 (1_1), TP8.1 (1_1)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
HA: J1.1, U4.3
HA_IN: A1.12 (D9), U4.1
HB: J3.1, U4.8
HB_IN: A1.14 (D11), U4.9
I2C_SCL: A1.24 (A5), A2.24 (A5), R10.2
I2C_SDA: A1.23 (A4), A2.23 (A4), R11.2
INV_CMD: D11.2 (A), J15.3, R39.2
INV_D4: A1.7 (D4), R39.1
I_AC: A1.21 (A2), C20.1, R15.1
I_LIM: J6.5, R40.2, R41.1
I_OUT_A0_AUX: A2.19 (A0), R22.2
LA: J1.3, U4.6
LA_IN: A1.13 (D10), U4.4
LB: J3.3, U4.11
LB_IN: A1.6 (D3), U4.12
MISO_D12: A2.15 (D12), J8.4
MON_15V_A1: A2.20 (A1), C29.1, R43.2, R44.1
MOSI_D11: A2.14 (D11), J8.5
NEUTRO: C2.1, C3.1, J2.2, R29.1, R30.1, RV2.2, RV2.3
NEUTRO-GRID: A1.10 (D7), C4.1, C5.1, C8.1, C30.2, J17.2, R5.1, R6.1, RV1.2, RV1.3
unnamed: BZ1.2 (-), D2.2 (A), D10.1 (K), Q2.1 (C)
unnamed: C16.1, R7.2, R8.2, R17.1
unnamed: D3.2 (A), R32.1
unnamed: D4.2 (A), R34.1
unnamed: D5.2 (A), R35.1
unnamed: D6.2 (A), R36.1
unnamed: D7.2 (A), J31.2, Q4.3 (C)
unnamed: D10.2 (A), R23.1
unnamed: J4.1, R25.1
unnamed: J5.2, R18.2, R19.1
unnamed: J6.1, R22.1
unnamed: J30.T, R15.2
unnamed: Q1.2 (B), R16.2
unnamed: Q2.2 (B), R20.2, R21.2
unnamed: Q4.2 (B), R33.2, R37.2
unnamed: R1.2, R2.1
unnamed: R2.2, R3.1, R4.2
unnamed: R8.1, RV1.1
unnamed: R9.1, RV2.1
P9_A: J1.5, R13.1
P9_B: J3.5, R14.1
SCK_D13: A2.16 (D13), J8.6
SCL_LCD: A2.8 (D5), J7.1
SDA_LCD: A2.7 (D4), J7.2
TEMP_A1: A1.20 (A1), C9.1, R19.2
TN_CMD: A1.16 (D13), J15.7

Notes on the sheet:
MONTAJE
TERMINALES 15V PARA GD A,B
Mouser N.º: 511-L7805CD2T-TR Fabricante N.º: L7805CD2T-TR
BUZER
P9_A P9_B Voltaje en A7 Firmware Abierto Abierto 5.00 V 1 µs Abierto GND 3.33 V 1 µs + “DT MIXTO (A)” GND Abierto 2.50 V 1 µs + “DT MIXTO (B)” GND GND 2.00 V 500 ns (solo si la lectura cae entre 1.8 y 2.2 V)
MONITOR RIEL 15V → A1 AUX (DC-008)
REGULADOR 5V TO220/SMD
PULL-UP BOTÓN LCD
BUCK 15 V → 8 V (MP1584)
ADC AC FB GRID
MICROCONTROLADORES: AUX (A2) Y CRÍTICO (A1) · PULL-UPS I2C · DESACOPLE 1 µF (DC-012)
CAÍDA AUTOMÁTICA A LA RED (DC-019)
CORTE DEL PWM POR HARDWARE (DC-014) Y P9 (DC-011)
CAN CON EL BMS (MCP2515 + RJ45)
BUCK 48 V → 15 V (XL7015)
J15 → TARJETA DE TRANSFERENCIA
VOLTAJE DE BATERÍA → A3 CRÍTICO
Si EN_HW = 0 (sensor, switch, AUX_KILL), D11 baja INV_CMD: la casa vuelve a la red aunque el CRÍTICO siga mandando INV. Banco: verificar que los relés suelten.
VENTILADORES
PULL-UPS I2C (A4/A5): 4.7kΩ a 5V — UN SOLO PAR PARA TODO EL BUS - I2C es de drenaje abierto: los chips solo jalan la línea a GND; sin pull-up la línea nunca sube a "1". - El Nano NO trae pull-ups en A4/A5. Los internos del ATmega (20–50kΩ) son muy débiles: flancos lentos y errores de lectura. - 4.7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
CAP JUNTO A7 EN PLACA
OPCIONAL ELECTRIOLITICO O X7R
Sensor DC V0.2, J6-5 (colector abierto). 0 V = en el límite. Pull-up aquí, a 5 V.
SENSOR AC (SCT-013-015) → A2 CRÍTICO
A7 del AUX no tiene pull-up interno.
I2C LCD BOTONERA
ADC AC FB INVERSOR
LÍMITE DE CORRIENTE I_LIM → D2 CRÍTICO
Pin Nano Puerto AVR Función en el código Va a Frecuencia D9 PB1 (OC1A) PIN_A_HI HIN del gate driver de la rama A 24 kHz (SPWM) D10 PB2 (OC1B) PIN_A_LO LIN del gate driver de la rama A 24 kHz (complementario) D11 PB3 PIN_B_HI HIN del gate driver de la rama B 60 Hz D3 PD3 PIN_B_LO LIN del gate driver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
15 V → 2.63 V. Llega a 5 V con 28.5 V. Aviso <13.5 o >16 V; paro <12 o >17 V.
TEMPERATURA (NTC 10K) → A1 CRÍTICO
INDICADOR LED

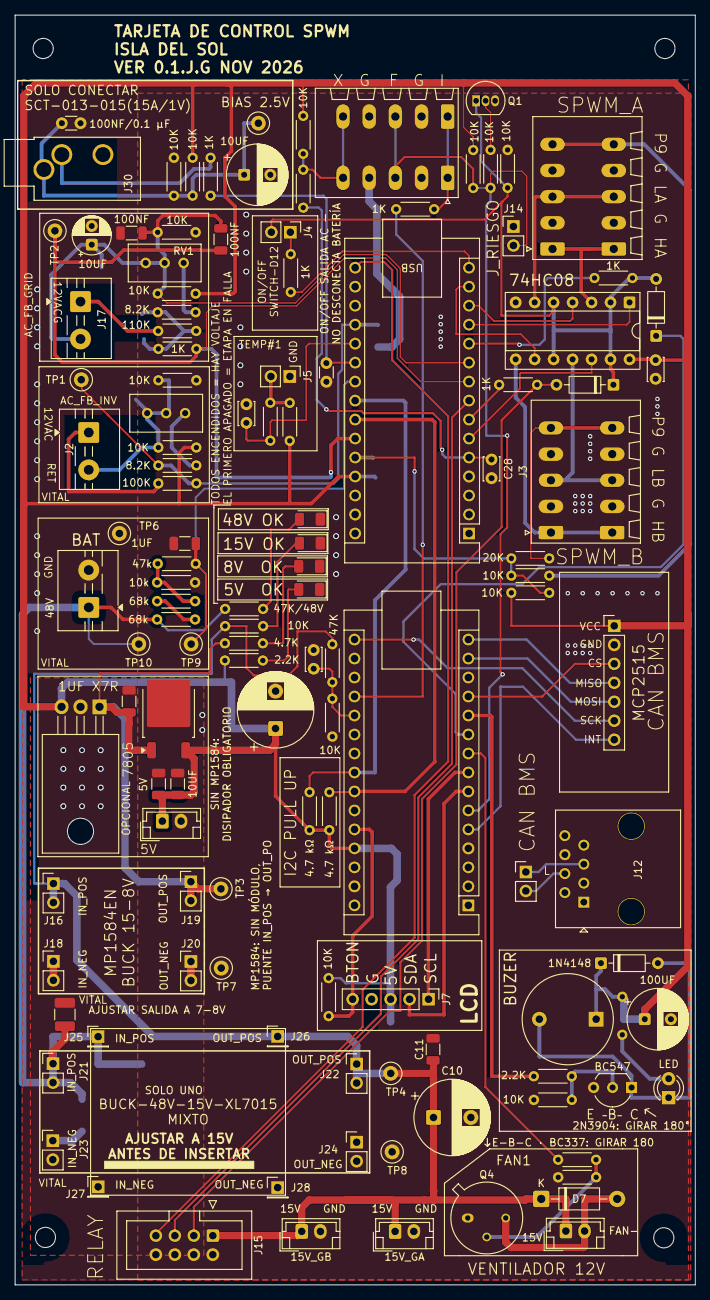
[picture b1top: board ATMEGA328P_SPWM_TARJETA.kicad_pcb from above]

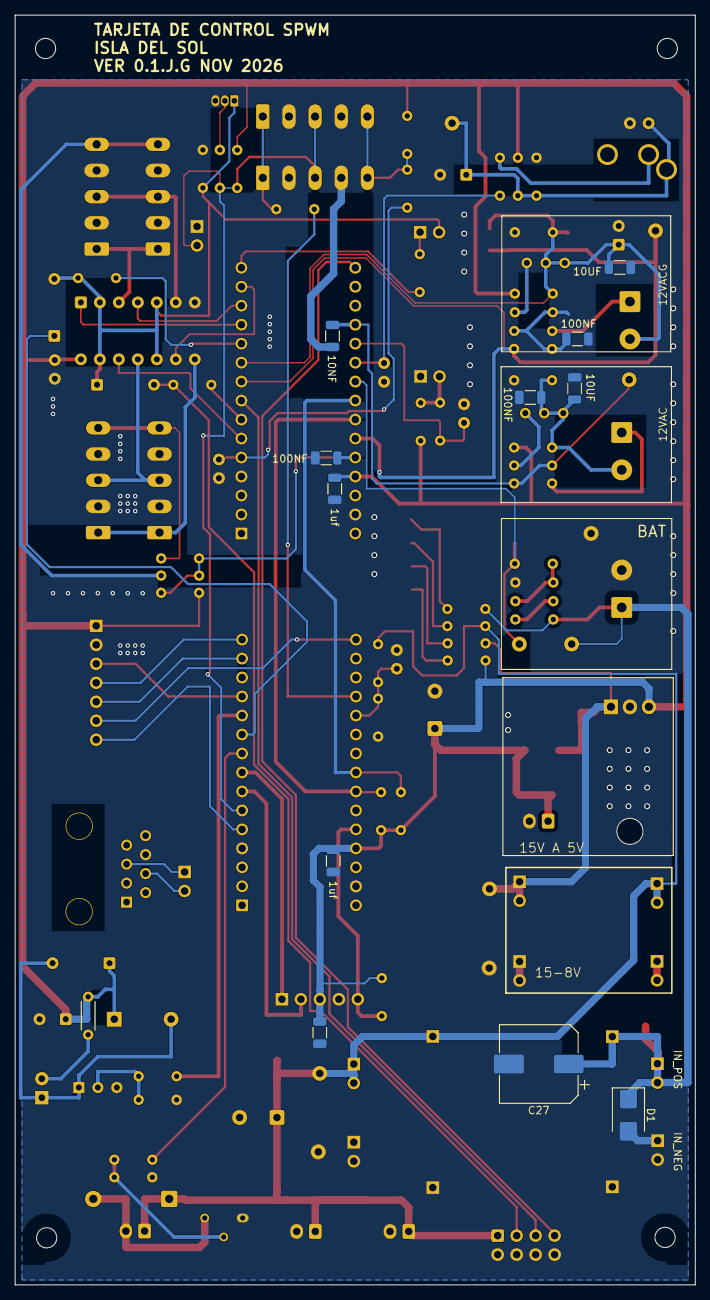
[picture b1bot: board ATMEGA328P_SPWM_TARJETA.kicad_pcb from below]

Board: 2 copper layers, 91.0 x 169.9 mm, 139 parts (12 on the bottom side), 72 nets.

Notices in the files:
README.md:
Licencia:
- **Hardware** (archivos de KiCad, Gerbers): CERN-OHL-S v2
- **Documentación**: CC BY-SA 4.0
- **Firmware**: MIT
Ver [`LICENSE.md`](LICENSE.md).
Antes de mandar un cambio**, lee [`CONTRIBUTING.md`](CONTRIBUTING.md). Son siete reglas y ninguna es de estilo: cada una dice qué falló cuando no estaba.
Las hojas de datos de los fabricantes no se incluyen en el repositorio por derechos de autor; los documentos citan la fuente de cada dato.
hardware/puente_h/README.md:
Hardware bajo licencia CERN-OHL-S v2; documentación CC BY-SA 4.0 (ver `LICENSE.md` en la raíz).
